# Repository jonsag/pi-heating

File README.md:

# pi-heating

Some scripts tweaked from https://github.com/JeffreyPowell, and many others created by me.  

Also there are CAD drawings and PCB layouts to build the electrical parts.  

Eventually you will have a Raspberry Pi that:

* controls (for example) a heater
* measures and logs your electric power consumption
* measures and logs numerous temperatures
* measures and logs wind direction and speed
* measures and logs rain
* presents it all via web GUI with some nice graphs
* also presents it on LCD displays
* can export logs to (spreadsheet or) csv

Let's start it all by

## Installing OS

Download 'Raspberry Pi OS Lite' from [https://www.raspberrypi.com/software/operating-systems/](https://www.raspberrypi.com/software/operating-systems/)  

Cd to where your download is and unpack it  
>$ unzip *-raspios-buster-armhf-lite.zip  

Insert SD-card and find out drive letter  
>$ dmesg  

For example /dev/mmcblk0 or /dev/sdb  

Unmount if mounted  
>$ umount /dev/mmcblk0p1  

Write image to SD-card  
>$ sudo dd bs=4M if=<version\>-raspios-buster-armhf-lite.img of=/dev/<device\> conv=fsync status=progress  

    1870659584 bytes (1,9 GB, 1,7 GiB) copied, 105 s, 17,8 MB/s  
    447+0 records in  
    447+0 records out  
    1874853888 bytes (1,9 GB, 1,7 GiB) copied, 139,716 s, 13,4 MB/s  

Remove SD-card and insert it again to make new partitions visible  

Mount the first partition  
>$ sudo mount /dev/<device\>1 /mnt/tmp  

Write empty file to boot partition to enable ssh at boot  
>$ sudo touch /mnt/tmp/ssh  

Remove SD-card and insert it in a RPi connected to your local network and boot it up  

## RPi configuration

### How to find RPi's IP

If you can't locate the IP, here's a little tutorial  

First find your subnet  
>$ ip -o -f inet addr show | awk '/scope global/ {print $4}'  

You will get something like  

    192.168.10.39/24  

where the first of is your ip, and the second is the netmask  

Now scan your local network for hosts  
>$ nmap -snP 192.168.10.0/24  

where the first is your subnet, and the last is the netmask  
Try to figure out which is your RPi from the output  

### How to connect without ssh password (optional)

If you haven't already, create a keypair  
>$ ssh-keygen ~/.ssh/id_rsa  

Copy the public key to RPi  
>$ ssh-copy-id -i ~/.ssh/id_rsa.pub pi@<IP\>  

### Connect and configure

>$ ssh <IP\> -l pi  

Login with user: pi and password:raspberry  

Update  
>$ sudo apt-get update && sudo apt-get upgrade && sudo apt autoremove  

Configure  
>$ sudo raspi-config  

* 1 S3 Change password  
* 1 S4 Change hostname  
* 3 P7 Enable 1-wire at boot  
* 4 P2 Set GPU memory to 16  
* 5 L1 Set locales (I chose en_GB.UTF-8 and sv_SE.UTF-8, setting en_GB.UTF-8 as default)  
* 5 L2 Set time zone  
* 5 L3 Choose keyboard layout (not necessary if you only connect by ssh)  
* 5 L4 Set wifi country  
* 6 A1 Expand file system to use whole SD-card  

Reboot to set new options  
>$ sudo reboot && exit  

Now it's time to:

## Download sources

Connect to the RPi again  
Install git, if you haven't already  
>$ sudo apt install git -y  

Make sure you're in pi's home directory  
>$ cd /home/pi  

Download source files  
>$ git clone [https://github.com/jonsag/pi-heating.git](https://github.com/jonsag/pi-heating.git)  

## Installation

Go to the newly downloaded directory  

>$ cd pi-heating

and run the install script  

>$ sudo ./install.sh  

The script will ask you many questions, and you will have some options on each:  

* Click enter to accept the default 'yes'  
* Enter 'n' or 'N' to decline  
* Enter 'h' or 'H' to view the help explanation  

Also you will have to answer some questions during the installs themselves, especially when MariaDB is installed.  

## Post install setup

## piHeatingHub

In a browser, go to  

    http://<IP>:8080/status.php  

### Adding sensors

Click  

    Input Sensors

and then  

    Scan for new sensors

After scanning click  

    Done

### Adding devices

Click  

    Output Devices

Click  

    Add new

Click  

    Edit

on the new one just added.  
Fill in all the fields and then click  

    Save

and then  

    Done

twice.  

Note: Pin numbers are used, NOT GPIO numbers.  

If using the piHeatingLCD hat, the one output device is at GPIO15, pin 10, and it it active HIGH, so you would set H/L to 1.  
Follow further instructions under piHeatingLCD  

## piHeatingRemote

After connecting Dallas temperature sensors,  
find 1-wire devices serial numbers  

>$ ls /sys/bus/w1/devices/  

Edit  

    /home/pi/bin/piHeatingRemote/configs/sensors

and insert serials and names, for example  

    28-0516b4ff09ff = Out  

To see value  

>$ cat /sys/bus/w1/devices/28-0416c1ec26ff/w1_slave  

See how many devices added  

>$ curl localhost:8081/count.php && echo  

See names  

>$ curl localhost:8081/name.php?id=1 && echo  

change id=1 to id=2 etc  

See values  

>$ curl localhost:8081/value.php?id=1 && echo  

## piHeatingLCD

The LCD and buttons will work if:  

* you have a schedule that always keep a low temperature  
* you have a second schedule that pulls up the temperature at certain times  
* you have a single mode that pulls up the temperature  
* you have a single timer that pulls up the temperature  

Build according to files in  

    Documents/piHeatingLCD

### Web setup

In a browser, go to  

    http://<IP>:8080/status.php

Log in with user 'admin' and the password you set up during the hub installation.  

### Add sensor

Add the sensor that will measure the temperature that will be regulated.  

Click  

    Input Sensors
    Scan for new sensors

When sensor is found, click  

    Done

### Add devices

Add the device that will control the heater.  

Click  

    Output Devices

Click  

    Add new

Click  

    Edit

on the newly added device.  
Set  

    Name: <name>
    GPIO Pin: 10
    Pin Active H/L: <if you use the NO, then this should be 1>

Click  

    Save
    Done
    Done

### Add mode

This mode will pull up the temperature to the higher level indefinitely.  

Click  

    Modes
    Add new

Click  

    Edit

on the newly added mode, and set  

    Name: <name>

, for example 'Warm' to indicate it will be used to pull up the temperature.

Then click  

    Done

### Add timer

This timer will be used to pull up the temperature for a certain amount of time.  

Click  

    Timers
    Add new

Ón the newly created timer, click  

    Edit

Set  

    Name: <name for the timer, for example 'Warm 6 hrs'>
    Duration: <the duration the timer will be active, in minutes,for example '360'>

, then click  

    Save
    Done
    Done

### Add schedules

The first schedule will pull up the temperature once, or several times, a week.  

Click  

    Schedules
    Add new

Click  

    Edit

on the newly created schedule.  

Enter

    Name: <name, for example 'Weekly meeting'>
    Start time: <some time before the temperature must be reached>
    End time: <the time when the temperature can start dropping>
    Repeat schedule every: <the day in question>
    When sensors: <sensor created earlier> IS LESS THAN <the high temperature you want to maintain>
    AND Timers: <timer previously added> STOPPED
    Activate Devices:<mark the device you created before>
    AND Modes: <mode previously added> OFF

Click  

    Save
    Done

The second schedule will use the mode created earlier to pull up the temperature indefinitely  

Add another timer as before and enter

    Name: <name, for example 'Warm'>
    Start time: 00:00:00
    End time: 23:59:59
    Repeat schedule every: <mark all weekdays>
    When sensors:  <sensor created earlier> IS LESS THAN <the high temperature you want to maintain>
    AND Timers: <timer previously added> (IS IGNORED)
    Activate Devices: <mark the device you created before>
    AND Modes: <mode previously added> ON

Click  

    Save
    Done

The third schedule will use the timer created earlier to pull up the temperature the time set  

Add another timer as before and enter

    Name: <name, for example 'Warm, 6 hrs'>
    Start time: 00:00:00
    End time: 23:59:59
    Repeat schedule every: <mark all weekdays>
    When sensors:  <sensor created earlier> IS LESS THAN <the high temperature you want to maintain>
    AND Timers: <timer previously added> RUNNING
    Activate Devices: <mark the device you created before>
    AND Modes: <mode previously added> (IS IGNORED)

Click  

    Save
    Done

The fourth, and last, schedule will keep the temperature low at all other times

Add another schedule as before and enter

    Name: <name, for example 'Cold'>
    Start time: 00:00:00
    End time: 23:59:59
    Repeat schedule every: <mark all weekdays>
    When sensors: <sensor created earlier> IS LESS THAN <the low temperature you want to maintain>
    AND Timers: <timer previously added> STOPPED
    Activate Devices: <mark the device you created before>
    AND Modes: <mode previously added> OFF

Click  

    Save
    Done
    Done

### Resources

Calculate burden resistor for your current clamp

>$ python resistor.py \<resistance\> \<tolerance\>  

### Usage

The LCD screen stays dark, unless pressing a button.  

* Button 1: Shows status  
* Button 2: Toggles mode, heats indefinitely  
* Button 3: Toggles timer, heats for set time  
* Button 4: Cancels both mode and timer  

### Note

If you install on Raspberry Pi rev 1, you must edit  

    piHeatingLCD/config.ini

Change line from  

    lcd_d6        = 27

to  

    lcd_d6        = 21

## piPowerTempLog

Build according to files in  

    Documents/ardPowerTempLog

This build requires an ethernet shield.  

## piWeatherLog

Build according to files in  

    Documents/ardWeatherLog

Connect the Arduino Weather Sensor to RPi  

Find out tty-device  

>$ dmesg | grep tty  

Probably named something like '/dev/ttyACM0'  
If not, edit  

    /var/www/piWeatherLog/weather.php  

Change line  

    $serial->deviceSet("/dev/ttyACM0");  

In file  

    /home/pi/bin/piWeatherLog/cron/bootWrapper.sh  

change lines  

    stty -F /dev/ttyACM0 cs8 9600 ign...  

and  

    screen -d -m -S init /dev/ttyACM0 9600

so it matches the output from dmesg command  

## The electrical builds

For all electrical builds there are CAD files for each project under 'Documentation'.  
Not all have finished PCB etch masks available as pdf.  
If you like to make some yourself, install KiCad ([https://www.kicad.org](https://www.kicad.org)) and just make them.  
I have made all as single layer PCBs myself, but just go ahead and route some double layered ones.  
If you don't want to make them them yourself, I can recommend JLCPCB ([https://jlcpcb.com](https://jlcpcb.com)), reasonably fast and very cheap.  

### piHeatingLCD

### ardPowerTempLog

This build also require some current clamps.  

I use three of these.  
If you go with other ones you will have to adapt your resistor values accordingly.  

Also, of course, you will need some DS18B20 1-wire temperature sensors.  

Other ones will also do, but then check what library and settings you use in the Arduino sketch.  
I have soldered cables directly to the pins, and connected it to a phono plug.  

Then you will need some device to catch the blinks on your power meter.  

### ardWeatherLog

I use an ordinary ethernet cable to connect the Arduino to the weather sensors.  

The sensors are some devices I got from a cheap weather station.  
  
I just tossed the LCD that went with it.  

## Install Arduino IDE

Install Arduino IDE from [https://www.arduino.cc/en/Main/Software](https://www.arduino.cc/en/Main/Software)  

>$ mv arduino-*.tar.xz ~/bin  
>$ cd ~/bin  
>$ tar -xvJf arduino-*.tar.xz  
>$ cd arduino-*  
>$ ./install.sh  

## Install Average library

Copy directory Average to your Arduino/libraries directory  

## Quick reference

### What is installed and where

Executables installed in  

    /home/pi/bin

Web GUI installed in  

    /var/www

Apache site configurations in  

    /etc/apache2/sites-enabled/

Apache listen directives in  

    /etc/apache2/ports.conf

Gpio service installed at  

    /lib/systemd/system/gpio.service

Extended boot parameters in  

    /boot/config.txt

Database at  

    /var/lib/mysql/piHeatingDB

Cron jobs in  

    /etc/cron.d/piHeating
    /etc/cron.d/piPowerTempLog

### Notes

piHeatingHub  

* executables installs in /home/pi/bin/piHeatingHub  
* www installs in /var/www/piHeatingHub  
* runs on port 8080  
* mysql setup creates password, and stores credentials /home/pi/bin/piHeatingHub/config/config.ini  
* secure install creates password for user 'admin', and stores it in /home/pi/bin/piHeatingHub/.htpasswd  
* runs cron job at /home/pi/bin/piHeatingHub/cron/wrapper.sh every minute  

piHeatingRemote  

* executables installs in /home/pi/bin/piHeatingRemote  
* www installs in /var/www/piHeatingRemote  
* runs on port 8081

piHeatingLCD  

* executables installs in /home/pi/bin/piHeatingLCD  
* requires gpio-watch  
* requires Adafruit Char LCD

piPowerTempLog  

* executables installs in /home/pi/bin/piPowerTempLog  
* www installs in /var/www/piPowerTempLog  
* runs on port 8082
* runs cron job at /home/pi/bin/piPowerTempLog/cron/wrapper.sh every 2 minutes  

piWeatherLog  

* executables installs in /home/pi/bin/piWeatherLog  
* www installs in /var/www/piWeatherLog  
* runs on port 8083
* runs cron job at /home/pi/bin/piWeatherLog/cron/wrapper.sh every 2 minutes  

### URLs

Hub:  
Pi heating hub status page: http://\<IP\>:8080/status.php  

Remote:  
Sensors count: http://\<IP\>:8081/count.php  
Sensor name for sensor #1: http://\<IP\>:8081/name.php?id=1  
Sensor value for sensor #1: http://\<IP\>:8081/value.php?id=1

Power log:  
Main page: http://\<IP\>:8082  

Weather log:  
Main page: http://\<IP\>:8083/weather.php

## Testing  

Below is only for my testing during development  
Use with caution!  

Upload source  

>$ rsync -avz --delete . pi@192.168.10.52:pi-heating/  

Upload piPowerTempLog www  

>$ rsync -avz . pi@192.168.10.52:/var/www/piPowerTempLog && ssh pi@192.168.10.52 "sudo chown pi:www-data /var/www/piPowerTempLog -R && sudo chmod 755 /var/www/piPowerTempLog/*.php"  

Upload piHeatingHub www  

>$ rsync -avz . pi@192.168.10.52:/var/www/piHeatingHub && ssh pi@192.168.10.52 "sudo chown pi:www-data /var/www/piHeatingHub -R && sudo chmod 755 /var/www/piHeatingHub/*.php"  

### On hub

View gpio.service  

>$ cat /lib/systemd/system/gpio.service  

View gpio script  

>$ cat /home/pi/bin/piHeatingLCD/gpio-scripts  

View gpio-watch log  

>$ tail -f ~/bin/piHeatingLCD/gpio-watch.log  

Test LCD  

>$ /home/pi/bin/piHeatingLCD/print-to-lcd.py -1 test1 -2 test2  

Simulate Button 1 press  

View config file  

>$ cat /home/pi/bin/piHeatingHub/config/config.ini  

Login to database  

>$ mysql -u pi -p$(cat /home/pi/bin/piHeatingHub/config/config.ini | grep password | awk '{ print $3 }') piHeatingDB  

using password from the above config  

Change ip on sensor  

>$ UPDATE sensors SET ip = 'new ip' WHERE ip = 'old ip';  

Set values for tty communications  

>$ stty -F /dev/ttyACM0 cs8 9600 ignbrk -brkint -imaxbel -opost -onlcr -isig -icanon -iexten -echo -echoe -echok -echoctl -echoke noflsh -ixon -crtscts

### On remote

Show sensor ids  

>$ ls /sys/bus/w1/devices/  

### Check Arduino output

Connect to arduino with screen:  

>$ screen /dev/ttyACM0 9600 -S \<session name>  

To get screen command prompt, enter  
[C-a] :  
Then type

    quit  

and [Return]  

or from outside of screen  

>$ screen -XS \<session name> quit  

Kill screen with ^ak or control-a k

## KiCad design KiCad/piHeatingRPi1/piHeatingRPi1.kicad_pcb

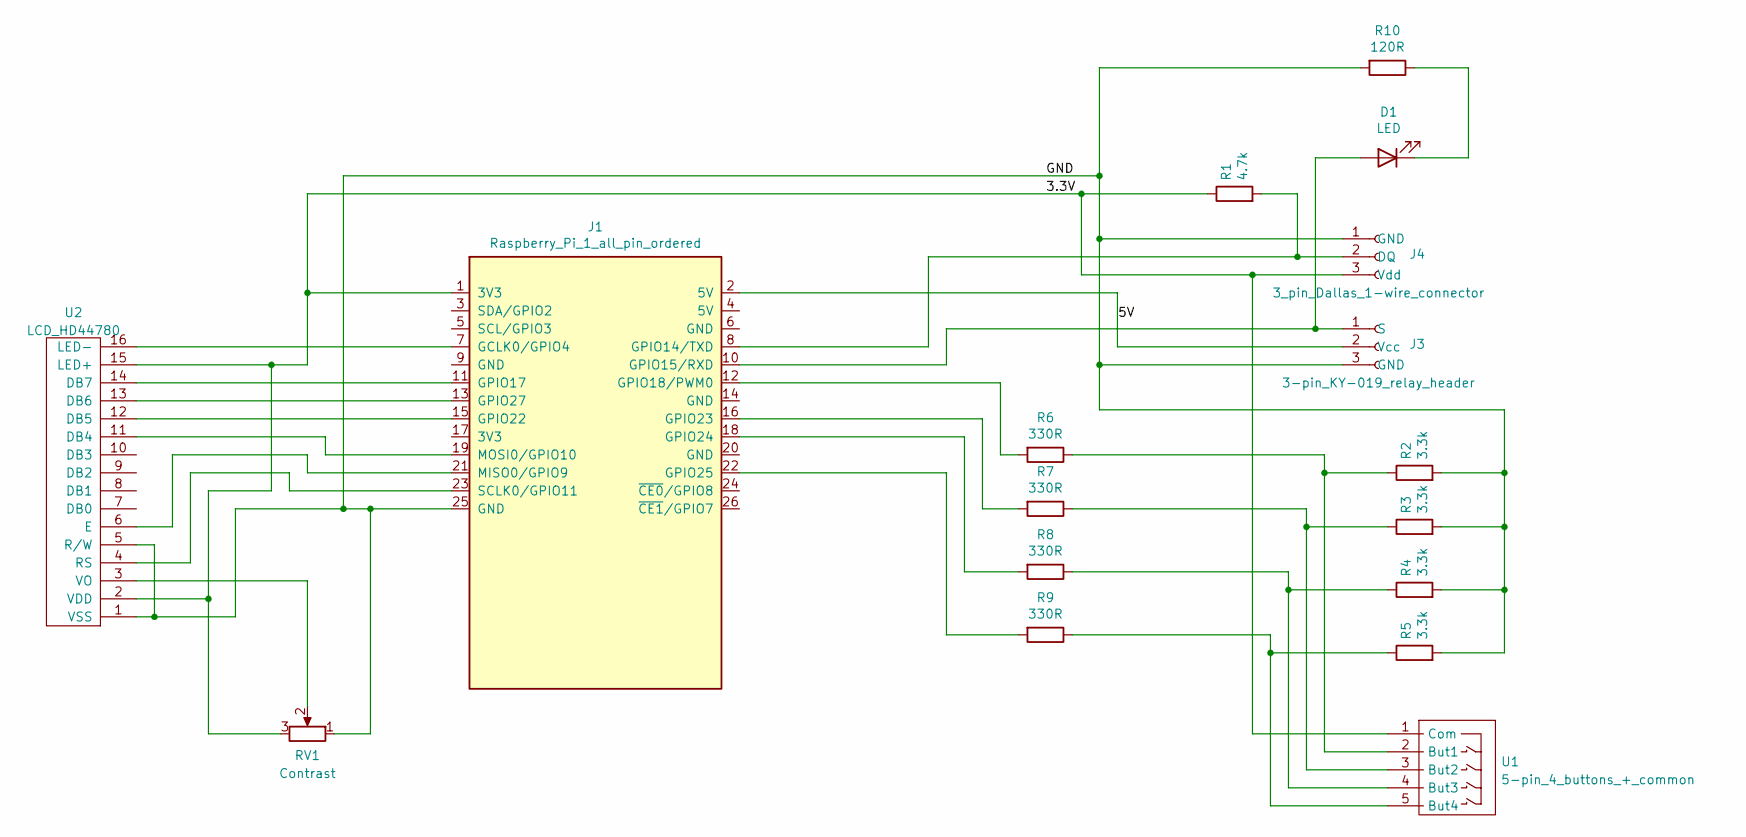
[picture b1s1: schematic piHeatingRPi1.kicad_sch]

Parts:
D1: LED; LED_D5.0mm_large
J1: Raspberry_Pi_1_all_pin_ordered; Raspberry_Pi_Hat_2x13_pin_GPIO_larger_pads
J3: 3-pin_KY-019_relay_header; 3-pin JST KY-019 relay
J4: 3_pin_Dallas_1-wire_connector; 3-pin JST DS18B20
R1: 4.7k; R_Axial_DIN0207_L6.3mm_D2.5mm_P10.16mm_Horizontal_larger_pa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
R2, R3, R4, R5: 3.3k; R_Axial_DIN0207_L6.3mm_D2.5mm_P10.16mm_Horizontal_larger_pa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
R6, R7, R8, R9: 330R; R_Axial_DIN0207_L6.3mm_D2.5mm_P10.16mm_Horizontal_larger_pa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
R10: 120R; R_Axial_DIN0207_L6.3mm_D2.5mm_P10.16mm_Horizontal_larger_pa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
RV1: Contrast; Potentiometer_Bourns_3339P_Vertical_large
U1: 5-pin_4_buttons_+_common; 5-pin JST 4 buttons + common
U2: LCD_HD44780; LCD_HD44780_16x2_w_headers_large

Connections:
/3.3V: J1.1 (3V3), J4.3 (Vdd), R1.1, RV1.3, U1.1 (Com), U2.2 (VDD), U2.15 (LED+)
/5V: J1.2 (5V), J3.2 (Vcc)
/GND: J1.25 (GND), J3.3 (GND), J4.1 (GND), R2.2, R3.2, R4.2, R5.2, R10.2, RV1.1, U2.1 (VSS), U2.5 (R/W)
unnamed: D1.1 (K), R10.1
unnamed: D1.2 (A), J1.10 (GPIO15/RXD), J3.1 (S)
unnamed: J1.7 (GCLK0/GPIO4), U2.16 (LED-)
unnamed: J1.8 (GPIO14/TXD), J4.2 (DQ), R1.2
unnamed: J1.11 (GPIO17), U2.14 (DB7)
unnamed: J1.12 (GPIO18/PWM0), R6.2
unnamed: J1.13 (GPIO27), U2.13 (DB6)
unnamed: J1.15 (GPIO22), U2.12 (DB5)
unnamed: J1.16 (GPIO23), R7.2
unnamed: J1.18 (GPIO24), R8.2
unnamed: J1.19 (MOSI0/GPIO10), U2.11 (DB4)
unnamed: J1.21 (MISO0/GPIO9), U2.6 (E)
unnamed: J1.22 (GPIO25), R9.2
unnamed: J1.23 (SCLK0/GPIO11), U2.4 (RS)
unnamed: R2.1, R6.1, U1.2 (But1)
unnamed: R3.1, R7.1, U1.3 (But2)
unnamed: R4.1, R8.1, U1.4 (But3)
unnamed: R5.1, R9.1, U1.5 (But4)
unnamed: RV1.2, U2.3 (VO)

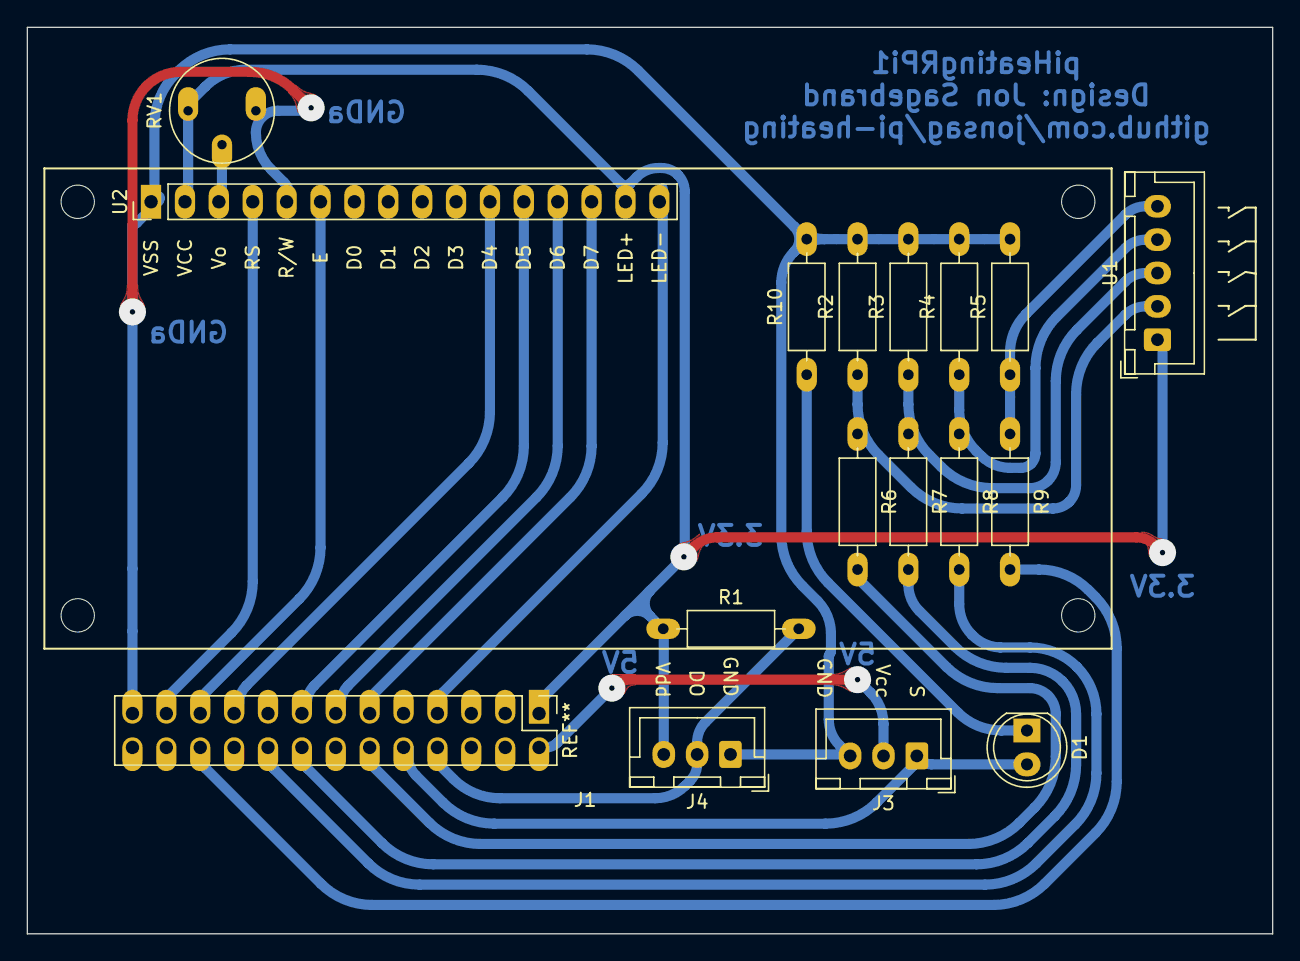
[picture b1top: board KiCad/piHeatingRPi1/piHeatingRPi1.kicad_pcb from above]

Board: 2 copper layers, 93.3 x 67.9 mm, 17 parts (0 on the bottom side), 22 nets.

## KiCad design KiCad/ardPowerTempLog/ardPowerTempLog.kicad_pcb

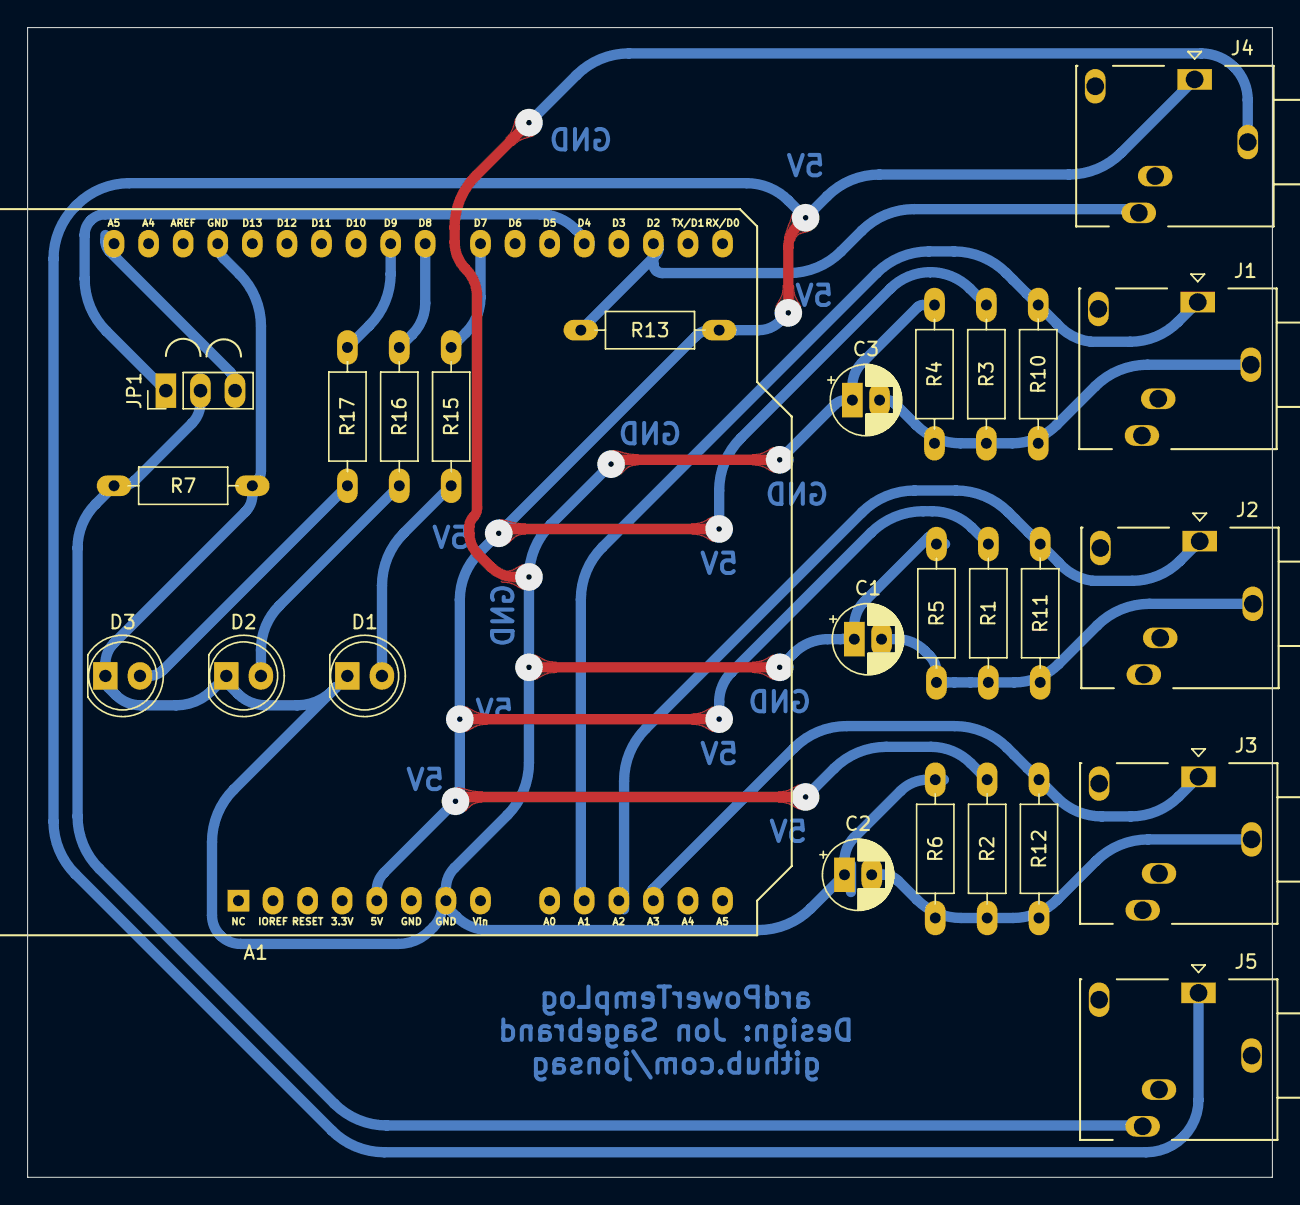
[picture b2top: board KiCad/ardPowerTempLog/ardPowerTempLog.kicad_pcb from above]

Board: 2 copper layers, 91.4 x 84.5 mm, 27 parts (0 on the bottom side), 18 nets.

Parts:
A1: Arduino_UNO_R3; Arduino_UNO_R3_shield_large
C1, C2, C3: 10u; CP_Radial_D5.0mm_P2.00mm_larger
D1: Status LED; LED_D5.0mm_large
D2: Polled LED; LED_D5.0mm_large
D3: Pulse LED; LED_D5.0mm_large
J1: R1; My_Jack_3.5mm_Ledino_KB3SPRS_Horizontal
J2: S2; My_Jack_3.5mm_Ledino_KB3SPRS_Horizontal
J3: T3; My_Jack_3.5mm_Ledino_KB3SPRS_Horizontal
J4: OneWire bus; My_Jack_3.5mm_Ledino_KB3SPRS_Horizontal
J5: LED sensor; My_Jack_3.5mm_Ledino_KB3SPRS_Horizontal
JP1: Analog/digital; Jumper_1x03_P2.54mm_large
R1, R2, R3, R4, R5, R6, R7: 10k; R_Axial_DIN0207_L6.3mm_D2.5mm_P10.16mm_Horizontal_larger_pa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
R10, R11, R12: 33R; R_Axial_DIN0207_L6.3mm_D2.5mm_P10.16mm_Horizontal_larger_pa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
R13: 4.7k; R_Axial_DIN0207_L6.3mm_D2.5mm_P10.16mm_Horizontal_larger_pa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
R15, R16, R17: 220R; R_Axial_DIN0207_L6.3mm_D2.5mm_P10.16mm_Horizontal_larger_pa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

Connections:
/Collector: A1.5 (+5V), J4.T, J5.T, R1.1, R2.1, R3.1, R13.2
/Data: A1.17 (D2), J4.S, R13.1
/Emitter: J5.S, JP1.2 (C), R7.2
/GND: A1.7 (GND), A1.29 (GND), C1.1, C2.1, C3.1, D1.1 (K), D2.1 (K), D3.1 (K), J4.G, R4.2, R5.2, R6.2, R7.1
unnamed: A1.10 (A1), J1.T, R10.1
unnamed: A1.11 (A2), J2.T, R11.1
unnamed: A1.12 (A3), J3.T, R12.1
unnamed: A1.19 (D4), JP1.1 (A)
unnamed: A1.22 (D7), R15.1
unnamed: A1.23 (D8), R16.1
unnamed: A1.24 (D9), R17.1
unnamed: A1.32 (SCL/A5), JP1.3 (B)
unnamed: C1.2, J2.G, R1.2, R5.1, R11.2
unnamed: C2.2, J3.G, R2.2, R6.1, R12.2
unnamed: C3.2, J1.G, R3.2, R4.1, R10.2
unnamed: D1.2 (A), R15.2
unnamed: D2.2 (A), R16.2
unnamed: D3.2 (A), R17.2

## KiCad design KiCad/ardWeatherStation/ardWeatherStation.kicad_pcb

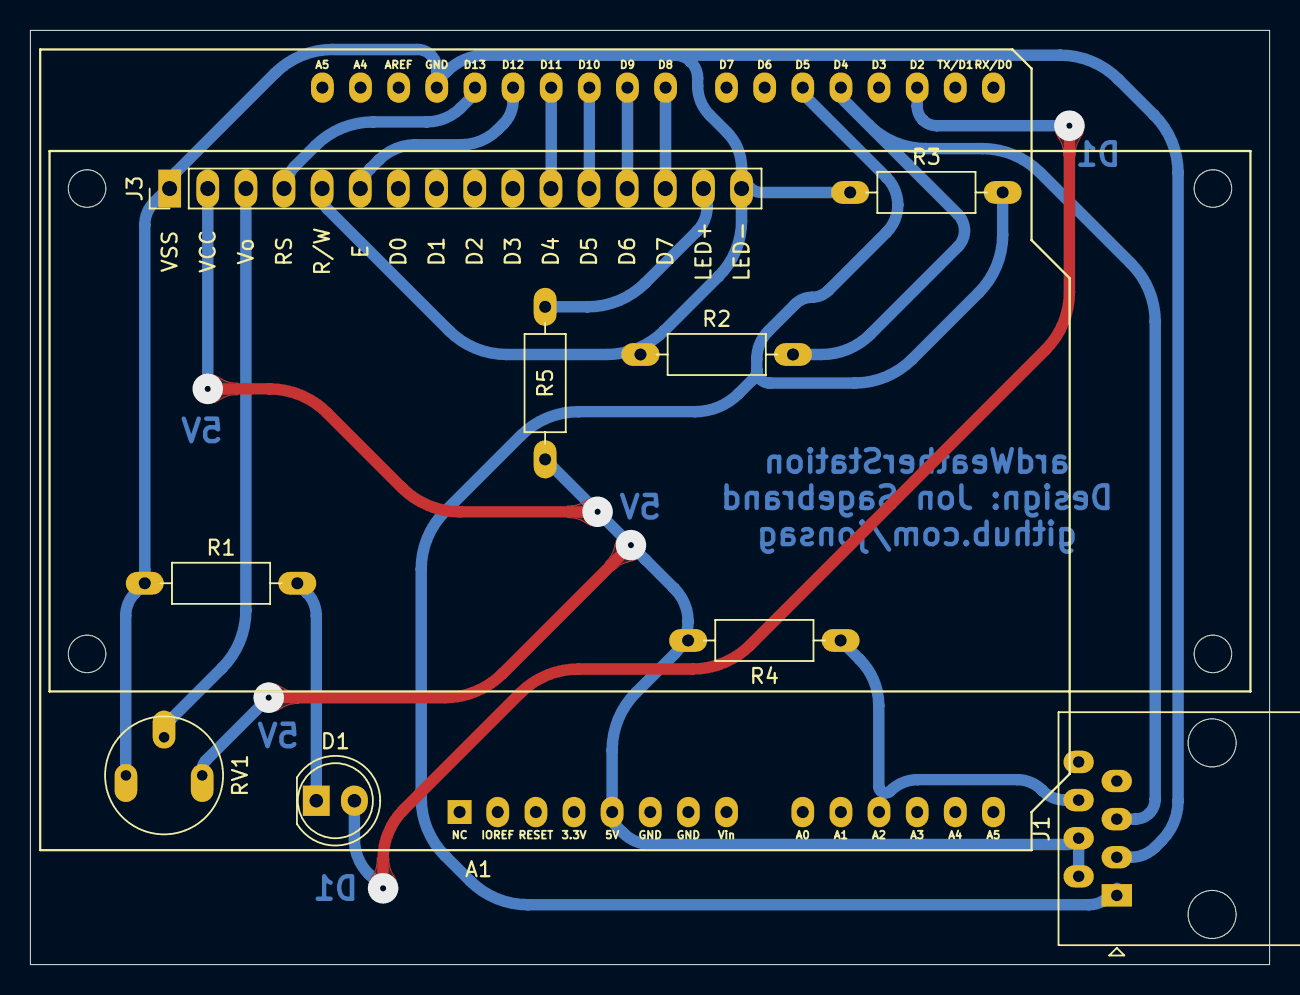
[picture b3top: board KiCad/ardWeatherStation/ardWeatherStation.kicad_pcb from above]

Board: 2 copper layers, 82.6 x 62.2 mm, 10 parts (0 on the bottom side), 15 nets.

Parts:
A1: Arduino_UNO_R3; Arduino_UNO_R3_shield_large
D1: LED; LED_D5.0mm_large
J1: RJ45; RJ45_Amphenol_54602-x08_Horizontal_large
J3: 16-pin_LCD_header; LCD_HD44780_16x2_w_headers_large
R1, R5: 330R; R_Axial_DIN0207_L6.3mm_D2.5mm_P10.16mm_Horizontal_larger_pa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
R2, R3: 10k; R_Axial_DIN0207_L6.3mm_D2.5mm_P10.16mm_Horizontal_larger_pa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
R4: 15k; R_Axial_DIN0207_L6.3mm_D2.5mm_P10.16mm_Horizontal_larger_pa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
RV1: 10k; Potentiometer_Bourns_3339P_Vertical_large

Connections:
/+5V: A1.5 (+5V), J1.2, J1.4, J3.2 (VCC), R4.2, R5.2, RV1.3
/GND: A1.29 (GND), J1.3, J3.1 (VSS), J3.5 (R/W), J3.16 (LED-), R1.1, R2.1, R3.1, RV1.1
unnamed: A1.11 (A2), J1.6, R4.1
unnamed: A1.17 (D2), D1.2 (A)
unnamed: A1.19 (D4), J1.5, R2.2
unnamed: A1.20 (D5), J1.1, R3.2
unnamed: A1.23 (D8), J3.14 (D7)
unnamed: A1.24 (D9), J3.13 (D6)
unnamed: A1.25 (D10), J3.12 (D5)
unnamed: A1.26 (D11), J3.11 (D4)
unnamed: A1.27 (D12), J3.6 (E)
unnamed: A1.28 (D13), J3.4 (RS)
unnamed: D1.1 (K), R1.2
unnamed: J3.3 (Vo), RV1.2
unnamed: J3.15 (LED+), R5.1

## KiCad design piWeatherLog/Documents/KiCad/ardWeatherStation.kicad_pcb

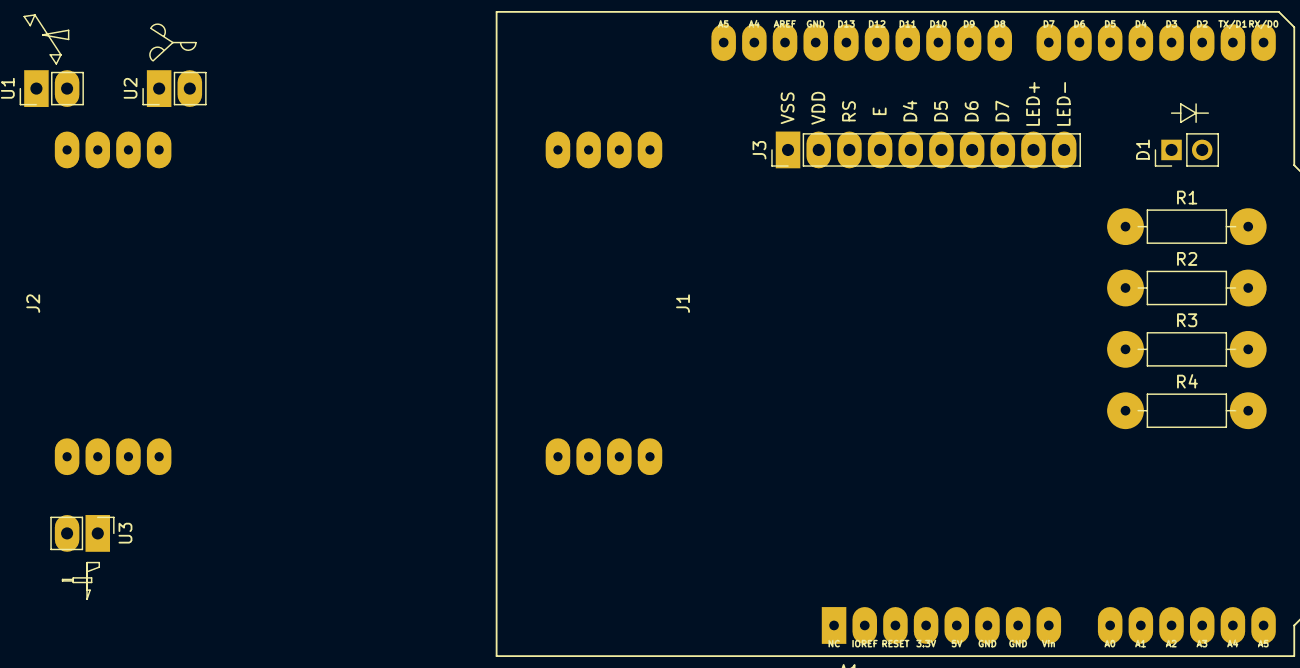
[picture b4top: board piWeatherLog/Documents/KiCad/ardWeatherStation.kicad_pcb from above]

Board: 2 copper layers, 12 parts (0 on the bottom side), 19 nets, no tracks yet.

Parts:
A1: Arduino_UNO_R3; Arduino_UNO_R3_shield_larger_pads
D1: LED; 2-pin_LED_header_large
J1, J2: RJ45; RJ45_cabled_large
J3: 10-pin_header_LCD_interface; 10-pin_LCD_header_larger_pads
R1: 330R; R_Axial_DIN0207_L6.3mm_D2.5mm_P10.16mm_Horizontal_larger_pa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
R2, R3: 10k; R_Axial_DIN0207_L6.3mm_D2.5mm_P10.16mm_Horizontal_larger_pa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
R4: 15k; R_Axial_DIN0207_L6.3mm_D2.5mm_P10.16mm_Horizontal_larger_pa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
U1: Rain_bucket; 2-pin_Rain_bucket_header_large
U2: Anemometer; 2-pin_Anemometer_header_large
U3: Wind_vane; 2-pin_Wind_vane_header_large

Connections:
unnamed: A1.5, J1.2, J1.4, J3.2, R4.2
unnamed: A1.11, J1.6, R4.1
unnamed: A1.17, D1.2
unnamed: A1.19, J1.5, R2.2
unnamed: A1.20, J1.1, R3.2
unnamed: A1.23, J3.8
unnamed: A1.24, J3.7
unnamed: A1.25, J3.6
unnamed: A1.26, J3.5
unnamed: A1.27, J3.4
unnamed: A1.28, J3.3
unnamed: A1.29, J1.3, J3.1, R1.1, R2.1, R3.1
unnamed: D1.1, R1.2
unnamed: J2.1, U2.2
unnamed: J2.2, U2.1
unnamed: J2.3, U3.1
unnamed: J2.4, U1.1
unnamed: J2.5, U1.2
unnamed: J2.6, U3.2

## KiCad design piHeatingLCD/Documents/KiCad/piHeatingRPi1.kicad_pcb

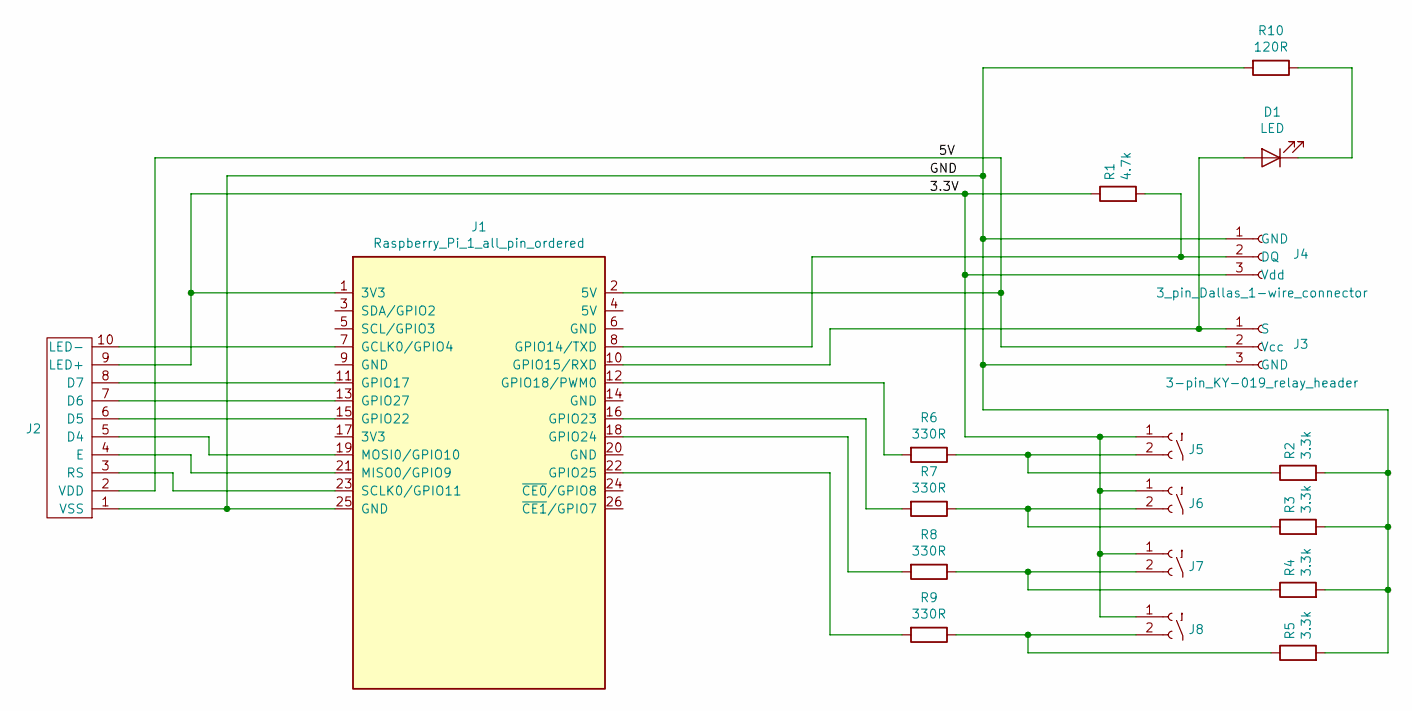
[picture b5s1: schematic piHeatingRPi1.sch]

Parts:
D1: LED; CP_Radial_D5.0mm_P2.50mm_larger_pads
J1: Raspberry_Pi_1_all_pin_ordered; Raspberry_Pi_Hat_2x13_pin_GPIO_larger_pads
J2: 10-pin_header_LCD_interface; 10-pin_LCD_header_larger_pads
J3: 3-pin_KY-019_relay_header; 3-pin_KY-019_Relay_header_larger_pads
J4: 3_pin_Dallas_1-wire_connector; 3_pin_Dallas_1-wire_header_larger_pads
J5, J6, J7, J8: 2-pin_NO_switch_header; 2-pin_NO_switch_header_larger_pads
R1: 4.7k; R_Axial_DIN0207_L6.3mm_D2.5mm_P10.16mm_Horizontal_larger_pa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
R2, R3, R4, R5: 3.3k; R_Axial_DIN0207_L6.3mm_D2.5mm_P10.16mm_Horizontal_larger_pa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
R6, R7, R8, R9: 330R; R_Axial_DIN0207_L6.3mm_D2.5mm_P10.16mm_Horizontal_larger_pa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
R10: 120R; R_Axial_DIN0207_L6.3mm_D2.5mm_P10.16mm_Horizontal_larger_pa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

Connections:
/3.3V: J1.1 (3V3), J2.9 (LED+), J4.3 (Vdd), J5.1 (+), J6.1 (+), J7.1 (+), J8.1 (+), R1.1
/5V: J1.2 (5V), J2.2 (VDD), J3.2 (Vcc)
/GND: J1.25 (GND), J2.1 (VSS), J3.3 (GND), J4.1 (GND), R2.2, R3.2, R4.2, R5.2, R10.2
unnamed: D1.1 (K), R10.1
unnamed: D1.2 (A), J1.10 (GPIO15/RXD), J3.1 (S)
unnamed: J1.7 (GCLK0/GPIO4), J2.10 (LED-)
unnamed: J1.8 (GPIO14/TXD), J4.2 (DQ), R1.2
unnamed: J1.11 (GPIO17), J2.8 (D7)
unnamed: J1.12 (GPIO18/PWM0), R6.2
unnamed: J1.13 (GPIO27), J2.7 (D6)
unnamed: J1.15 (GPIO22), J2.6 (D5)
unnamed: J1.16 (GPIO23), R7.2
unnamed: J1.18 (GPIO24), R8.2
unnamed: J1.19 (MOSI0/GPIO10), J2.5 (D4)
unnamed: J1.21 (MISO0/GPIO9), J2.4 (E)
unnamed: J1.22 (GPIO25), R9.2
unnamed: J1.23 (SCLK0/GPIO11), J2.3 (RS)
unnamed: J5.2 (Sig), R2.1, R6.1
unnamed: J6.2 (Sig), R3.1, R7.1
unnamed: J7.2 (Sig), R4.1, R8.1
unnamed: J8.2 (Sig), R5.1, R9.1

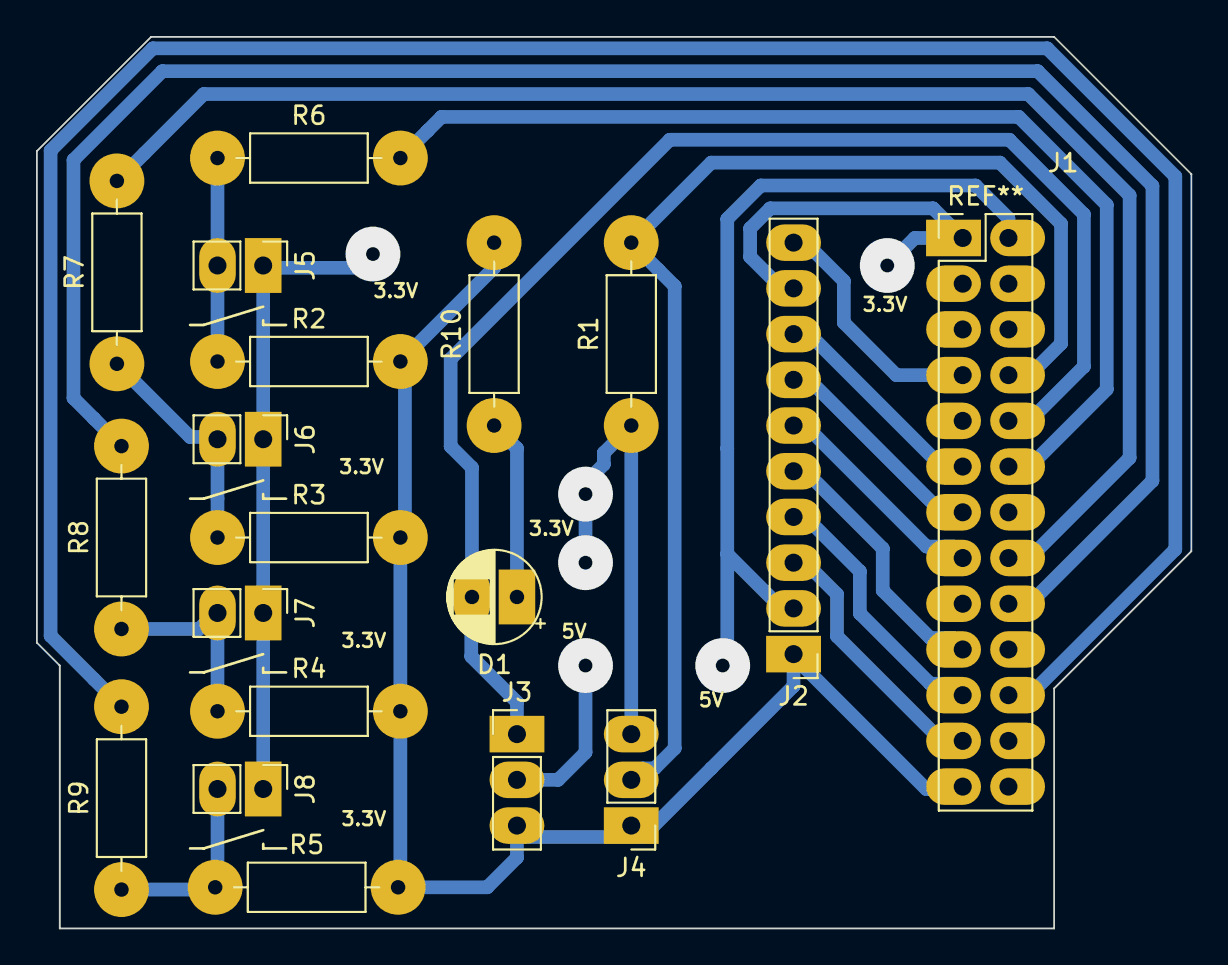
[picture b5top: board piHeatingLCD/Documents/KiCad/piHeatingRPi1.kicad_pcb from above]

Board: 2 copper layers, 64.1 x 49.5 mm, 19 parts (0 on the bottom side), 21 nets.

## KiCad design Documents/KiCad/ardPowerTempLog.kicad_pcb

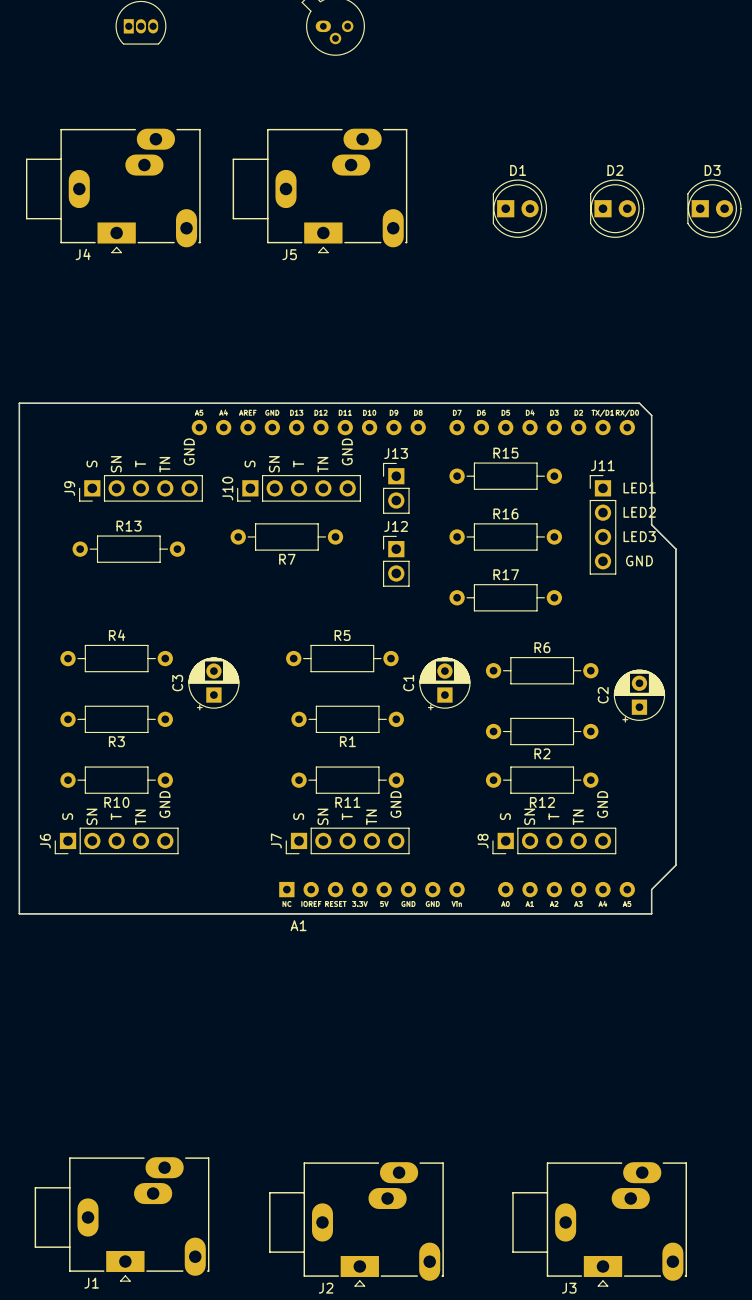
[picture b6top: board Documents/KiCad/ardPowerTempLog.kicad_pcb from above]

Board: 2 copper layers, 68.6 x 53.3 mm, 36 parts (0 on the bottom side), 18 nets, no tracks yet.

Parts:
A1: Arduino_UNO_R3; Arduino_UNO_R3_shield
C1, C2, C3: 10u; CP_Radial_D5.0mm_P2.50mm
D1: Status LED; LED_D5.0mm
D2: Polled LED; LED_D5.0mm
D3: Pulse LED; LED_D5.0mm
J1: R1; My_Jack_3.5mm_Ledino_KB3SPRS_Horizontal
J2: S2; My_Jack_3.5mm_Ledino_KB3SPRS_Horizontal
J3: T3; My_Jack_3.5mm_Ledino_KB3SPRS_Horizontal
J4: OneWire bus; My_Jack_3.5mm_Ledino_KB3SPRS_Horizontal
J5: LED sensor; My_Jack_3.5mm_Ledino_KB3SPRS_Horizontal
J6, J7, J8, J9, J10: 5-pin_3-pole_3,5mm_audio_header; 5-pin_3,5mm_audio_jack_header
J11: 4-pin_3LED_header; 4-pin_3_LED_header
J12, J13: Conn_01x02_Male; PinHeader_1x02_P2.54mm_Vertical
Q1: Q_Photo_NPN_CBE; TO-18-3
R1, R2, R3, R4, R5, R6: 10k; R_Axial_DIN0207_L6.3mm_D2.5mm_P10.16mm_Horizontal
R7: 1k; R_Axial_DIN0207_L6.3mm_D2.5mm_P10.16mm_Horizontal
R10, R11, R12: 33R; R_Axial_DIN0207_L6.3mm_D2.5mm_P10.16mm_Horizontal
R13: 4.7k; R_Axial_DIN0207_L6.3mm_D2.5mm_P10.16mm_Horizontal
R15, R16, R17: 220R; R_Axial_DIN0207_L6.3mm_D2.5mm_P10.16mm_Horizontal
U1: DS18B20; TO-92_Inline

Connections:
/Collector: A1.5, J4.T, J5.T, J9.3, J10.3, Q1.1, R1.1, R2.1, R3.1, R13.2, U1.3
/Data: A1.17, J4.S, J9.1, R13.1, U1.2
/Emitter: J5.S, J10.1, J12.1, J13.2, Q1.3, R7.2
/GND: A1.7, A1.29, C1.2, C2.2, C3.2, D1.1, D2.1, D3.1, J4.G, J9.5, J11.4, R4.2, R5.2, R6.2, R7.1, U1.1
unnamed: A1.10, J1.T, J6.3, R10.1
unnamed: A1.11, J2.T, J7.3, R11.1
unnamed: A1.12, J3.T, J8.3, R12.1
unnamed: A1.19, J13.1
unnamed: A1.22, R15.1
unnamed: A1.23, R16.1
unnamed: A1.24, R17.1
unnamed: A1.32, J12.2
unnamed: C1.1, J2.G, J7.5, R1.2, R5.1, R11.2
unnamed: C2.1, J3.G, J8.5, R2.2, R6.1, R12.2
unnamed: C3.1, J1.G, J6.5, R3.2, R4.1, R10.2
unnamed: D1.2, J11.1, R15.2
unnamed: D2.2, J11.2, R16.2
unnamed: D3.2, J11.3, R17.2
